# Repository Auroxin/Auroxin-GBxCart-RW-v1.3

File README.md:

# GBxCart RW v1.3 PCB Re-Layout

This project is a PCB re-layout based on the [insideGadgets GBxCart RW](https://www.gbxcart.com/) v1.3 hardware design, with improved component placement and PCB routing.

GBxCart RW can be used to read Game Boy, Game Boy Color, and Game Boy Advance cartridges, as well as to back up and restore cartridge save data. For software, firmware, usage instructions, and compatibility information, please visit the [official GBxCart RW website](https://www.gbxcart.com/) and the [official product page](https://shop.insidegadgets.com/product/gbxcart-rw/).

## Features of This Version

- Re-designed PCB layout based on the GBxCart RW v1.3 hardware
- Optimized component placement and PCB routing
- ENIG (Electroless Nickel Immersion Gold) surface finish
- Acrylic protective enclosure
- KiCad PCB project files and production-ready Gerber files included

## Repository Contents

- `PCB/` — KiCad project and PCB source files
- `Gerber/` — PCB manufacturing files
- `extras/` — Additional related files

## Purchase and Support

Assembled boards of this version are available for purchase on AliExpress. If you like this PCB re-layout and would like to support further development and maintenance, please consider purchasing one from my AliExpress store.

**[Purchase the assembled GBxCart RW v1.3 PCB on AliExpress](https://www.aliexpress.com/item/1005012667748987.html)**

## Acknowledgements

Special thanks to [insideGadgets](https://www.insidegadgets.com/) for creating and maintaining the GBxCart RW project. I would also like to thank every open-source developer and community member who has contributed to its hardware, firmware, software, documentation, and compatibility testing.

This PCB re-layout would not have been possible without their work and willingness to share it with the community. Please visit and support the [original GBxCart RW project](https://www.gbxcart.com/) and its creators.

## Disclaimer

This is an unofficial PCB re-layout based on the GBxCart RW v1.3 hardware. It is not affiliated with, endorsed by, or officially authorized by insideGadgets. The GBxCart RW name and original design belong to their respective owners.

Please use this device only to back up or manage cartridges and data that you legally own, and comply with all applicable laws in your jurisdiction. Use of the files in this repository is at your own risk.

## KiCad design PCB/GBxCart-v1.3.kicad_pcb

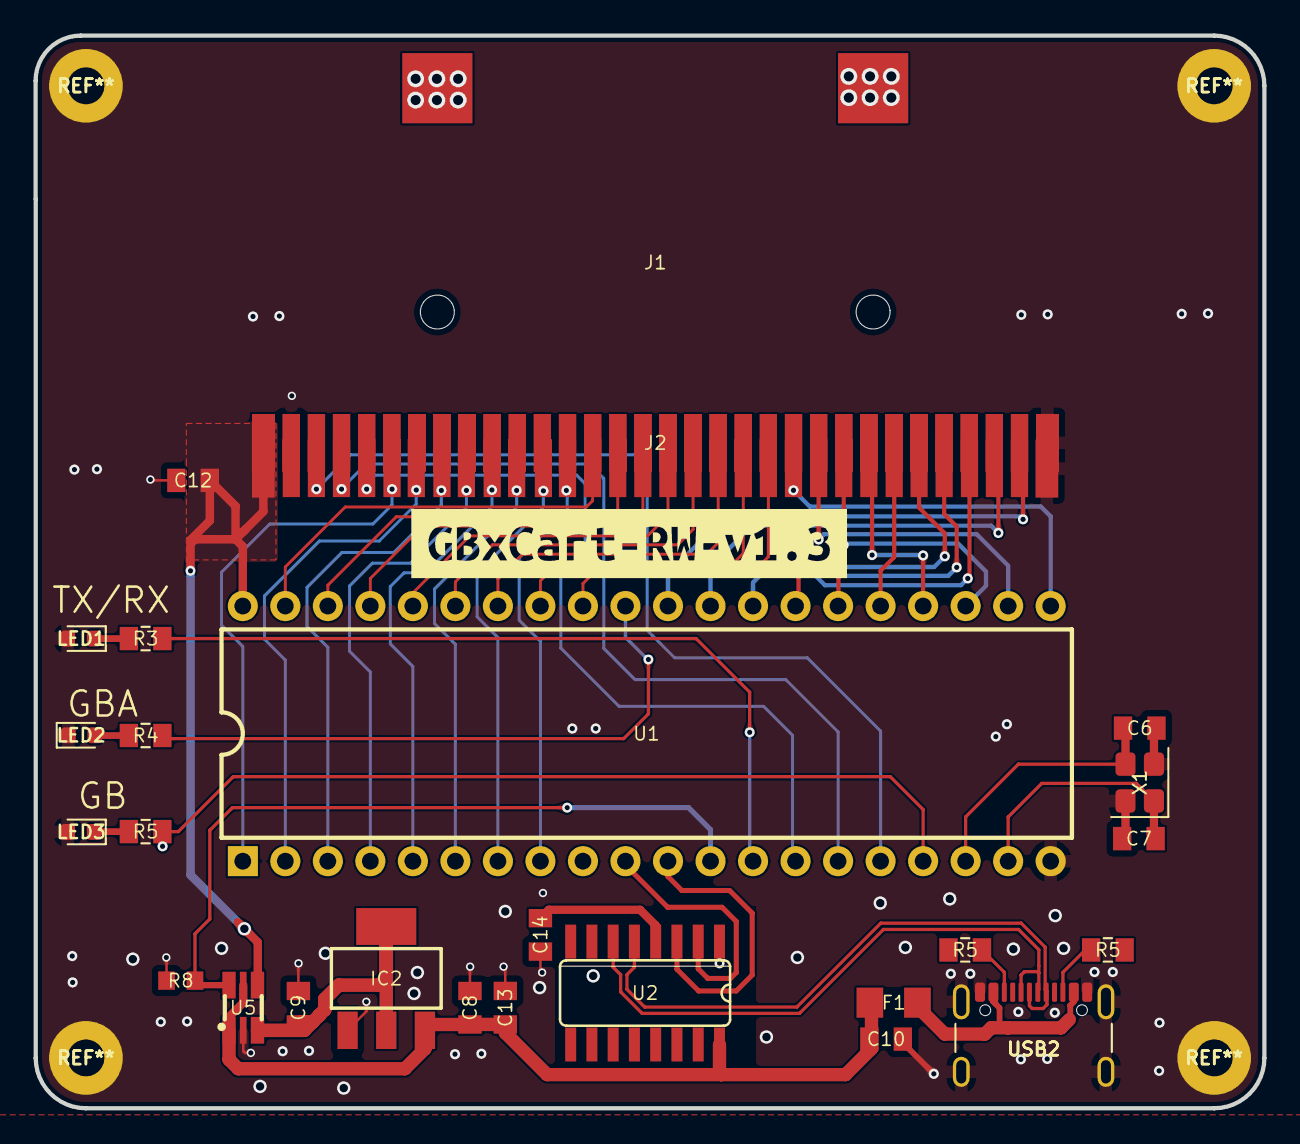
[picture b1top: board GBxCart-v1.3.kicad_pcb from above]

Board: 2 copper layers, 73.4 x 64.1 mm, 27 parts (0 on the bottom side), 50 nets.

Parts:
C6, C7, C8, C9, C10, C12, C13, C14: C0805K
F1: R1206
IC2: SOT223
J1: GB CARD SLOT
J2: GB_CART_1
LED1, LED2, LED3: LED_0603_1608Metric
R3, R4, R5, R5#2, R5#3: R0805_2
R8: R0603
U1: PDIP-40_L52.3-W13.8-P2.54-LS15.2-BL
U2: SO16
U5: SC-88-6_L2.0-W1.3-P0.65-LS2.1-BL
USB2: USB_C_Receptacle_GCT_USB4105-xx-A_16P_TopMnt_Horizontal
X1: Crystal_SMD_3225-4Pin_3.2x2.5mm
kibuzzard-6A1FD2AE: G***; kibuzzard-6A1FD2AE

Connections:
3.3V: C9.1, IC2.2, IC2.TAB, U5.3
3.3VLED: R4.1, U1.31
5V: C8.1, C10.1, C13.1, F1.2, IC2.3, U2.16, U5.1, U5.5
5VLED: R5#2.1, U1.17
*MREQ/CS: J1.5, J2.5, U1.14
*RD: J1.4, J2.4, U1.15
*RESET/CS2: J1.30, J2.30, U1.29
*WR: J1.3, J2.3, U1.16
A0: J1.6, J2.6, U1.1
A1: J1.7, J2.7, U1.2
A2: J1.8, J2.8, U1.3
A3: J1.9, J2.9, U1.4
A4: J1.10, J2.10, U1.5
A5/MOSI: J2.11, U1.6
A6/MISO: J2.12, U1.7
A7/SCK: J2.13, U1.8
A8: J1.14, J2.14, U1.39
A9: J1.15, J2.15, U1.38
A10: J1.16, J2.16, U1.37
A11: J1.17, J2.17, U1.36
A12: J1.18, J2.18, U1.35
A13: J1.19, J2.19, U1.34
A14: J1.20, J2.20, U1.33
A15: J1.21, J2.21, U1.32
ATMEGA_RXD_IN: U1.10, U2.2
ATMEGA_TXD_IN: U1.11, U2.3
AUDIO_IN: J1.31, J2.31, U1.30
CC1: R5#3.1, USB2.B8
CC2: R5.2, USB2.B5
D0: J1.22, J2.22, U1.21
D1: J1.23, J2.23, U1.22
D2: J1.24, J2.24, U1.23
D3: J1.25, J2.25, U1.24
D4: J1.26, J2.26, U1.25
D5: J1.27, J2.27, U1.26
D6: J1.28, J2.28, U1.27
D7: J1.29, J2.29, U1.28
GND: C6.2, C7.2, C8.2, C9.2, C10.2, C12.2, C13.2, C14.2, IC2.1, J1.2, J1.32, J2.32, LED1.2, LED2.1, LED3.2, R8.1, U1.20, U2.1, U5.2, USB2.A1, USB2.A12, USB2.B1, USB2.B12, USB2.SH, X1.2, X1.4
unnamed: LED2.2, R4.2
unnamed: LED3.1, R5#2.2
unnamed: LED1.1, R3.2
RX/TXLED: R3.1, U1.13
SPDT_SEL: R8.2, U1.12, U5.6
USB_D+: U2.5, USB2.A6, USB2.B6
USB_D-: U2.6, USB2.A7, USB2.B7
V3: C14.1, U2.4
VBUS: F1.1, USB2.A4, USB2.A9, USB2.B4, USB2.B9
VCC: C12.1, J1.1, J2.1, U1.40, U5.4
XTAL5: C6.1, U1.18, X1.3
XTAL6: C7.1, U1.19, X1.1
